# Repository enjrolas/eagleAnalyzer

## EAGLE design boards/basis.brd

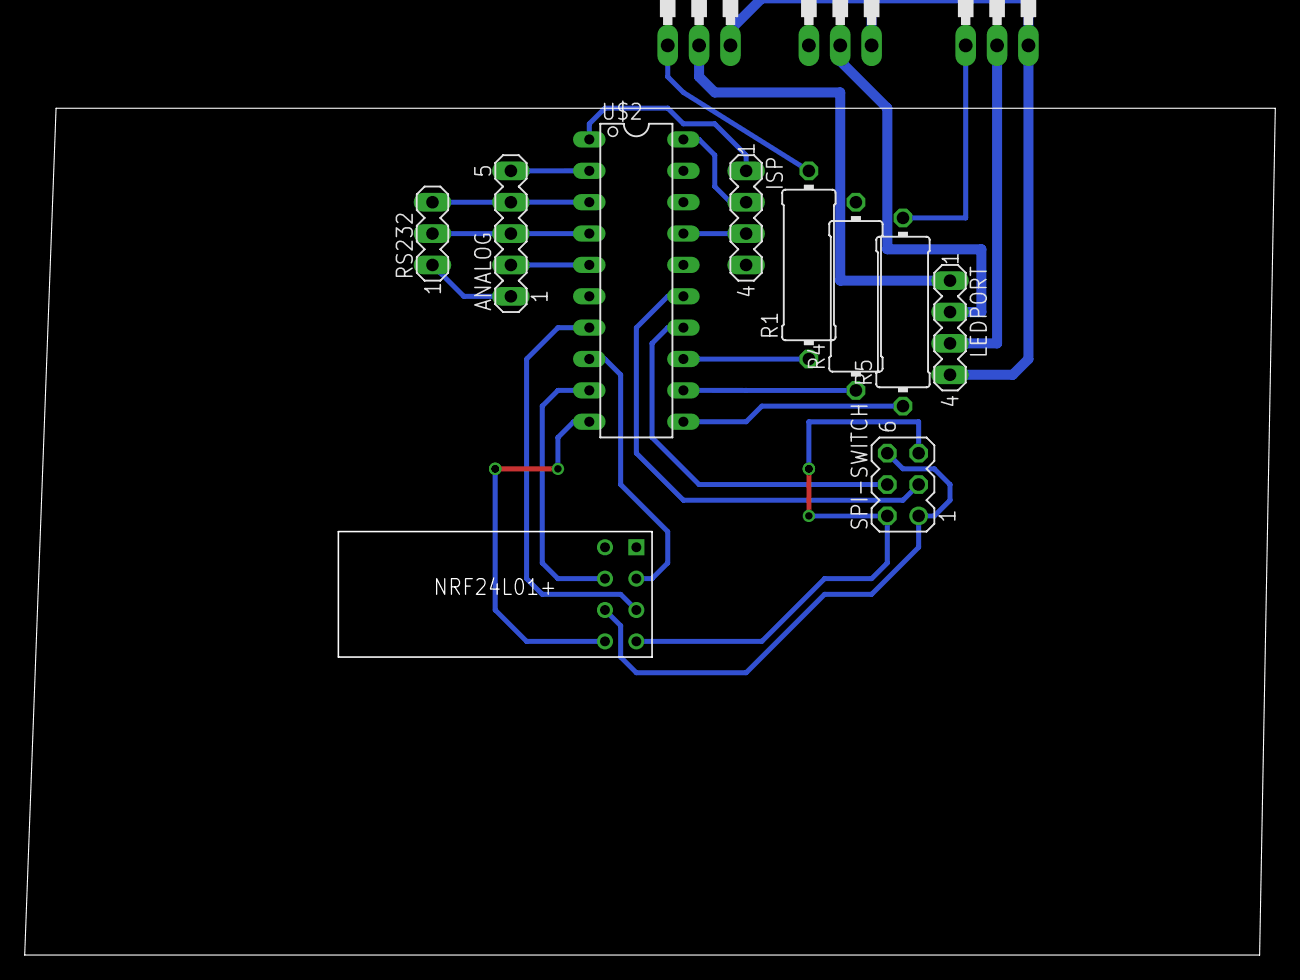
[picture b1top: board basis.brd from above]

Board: 2 copper layers, 13 parts (0 on the bottom side), 25 nets.

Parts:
ANALOG: 5PIN; MA05-1
ISP: 4PIN; MA04-1
LEDB: TIP122; TO220
LEDG: TIP122; TO220
LEDPORT: 4pin; MA04-1
LEDR: TIP122; TO220
R1, R4, R5: 1K; 0414/15
RS232: SERIAL; MA03-1
SPI-SWITCH: SPI; MA03-2
U$1: NFR24L01+-PRINT; MINI-PCB
U$2: G2XX3---N20; N20

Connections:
GND: ANALOG.1, ISP.2, LEDB.3, LEDG.3, LEDPORT.4, LEDR.3, RS232.1, U$1.GND, U$2.20
unnamed: U$1.SCK, U$2.7
unnamed: SPI-SWITCH.2, SPI-SWITCH.5, U$1.MISO
unnamed: SPI-SWITCH.4, U$2.14
unnamed: U$1.CE, U$2.8
unnamed: U$1.CSN, U$2.9
unnamed: U$1.IRQ, U$2.10
unnamed: SPI-SWITCH.3, U$2.15
unnamed: SPI-SWITCH.1, SPI-SWITCH.6, U$1.MOSI
unnamed: ANALOG.5, U$2.2
unnamed: ANALOG.4, RS232.3, U$2.3
unnamed: ANALOG.3, RS232.2, U$2.4
unnamed: ANALOG.2, U$2.5
unnamed: LEDR.1, R1.2
unnamed: LEDG.1, R4.2
unnamed: LEDB.1, R5.2
unnamed: R1.1, U$2.13
unnamed: R4.1, U$2.12
unnamed: R5.1, U$2.11
unnamed: LEDPORT.1, LEDR.2
unnamed: LEDG.2, LEDPORT.2
unnamed: LEDB.2, LEDPORT.3
TEST: ISP.3, U$2.17
VCC: ISP.1, U$1.VCC, U$2.1
_REST: ISP.4, U$2.16

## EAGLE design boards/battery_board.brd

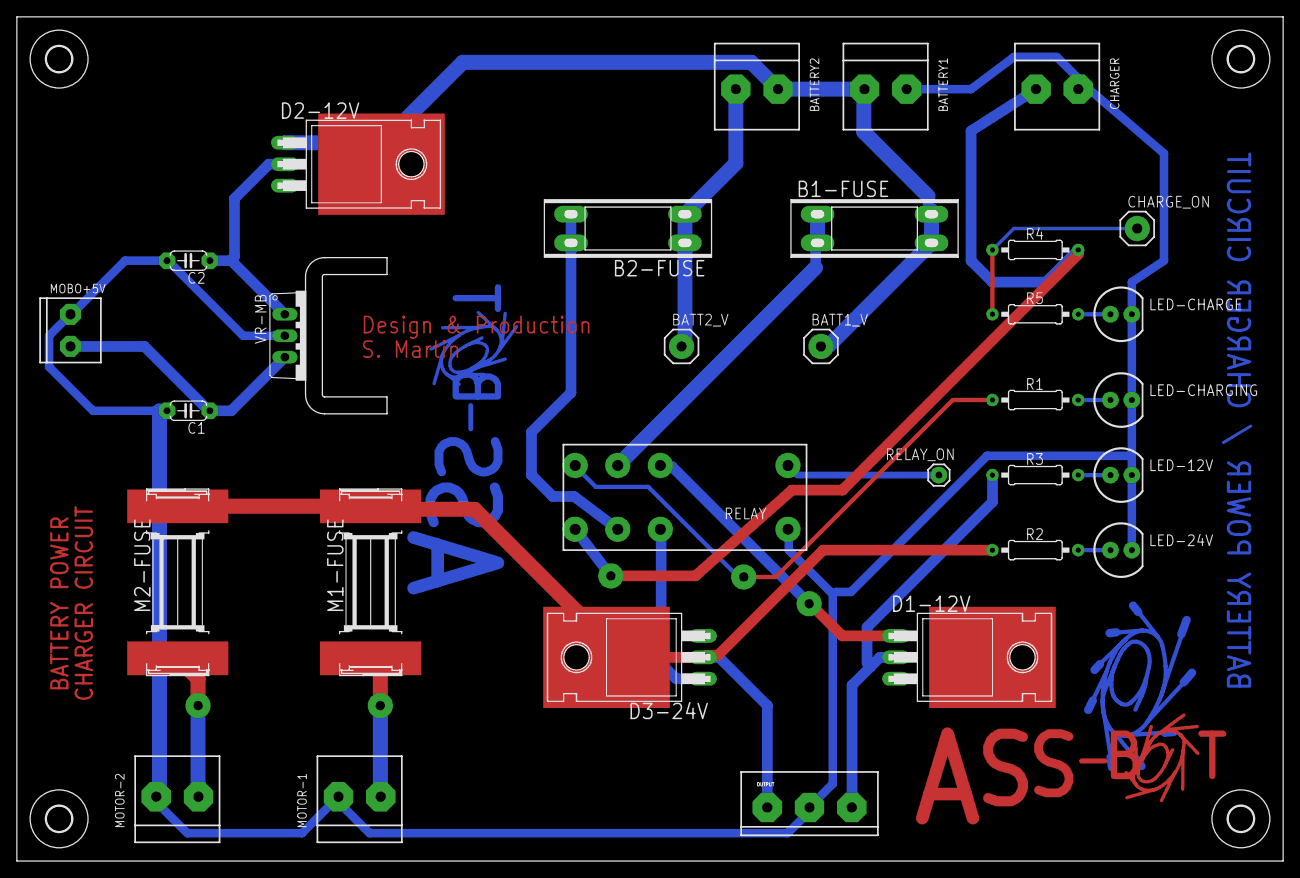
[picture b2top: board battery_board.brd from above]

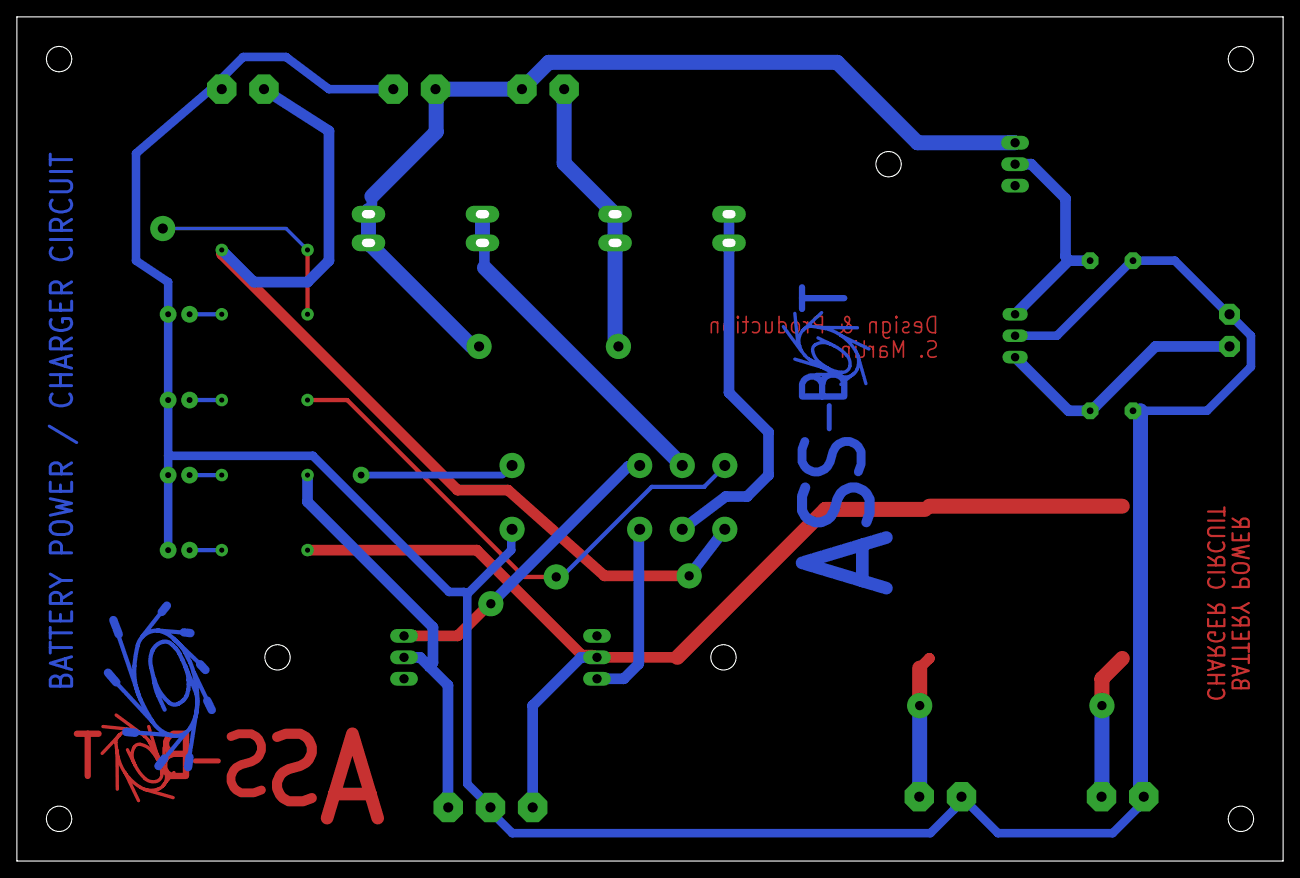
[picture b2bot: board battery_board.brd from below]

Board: 2 copper layers, 150.0 x 100.0 mm, 39 parts (2 on the bottom side), 21 nets.

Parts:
B1-FUSE, B2-FUSE: 20A; FUSE_BLADE
BATT1_V, BATT2_V: 1-HOLE; 1-HOLE_BIG
BATTERY1, BATTERY2: 12V; SCREWTERMINAL-5MM-2
C1: 10uF; C050-024X044
C2: 2.2uF; C050-024X044
CHARGER: 24V; SCREWTERMINAL-5MM-2
CHARGE_ON: 1-HOLE; 1-HOLE_BIG
D1-12V, D2-12V, D3-24V: 30A; TO22-DIODE-H
LED-12V, LED-24V: LED5MM
LED-CHARGE: LED5MM
LED-CHARGING: LED5MM
M1-FUSE, M2-FUSE: 3A; FUSE-5X20MM_SMD
MOBO+5V: 2-HOLESSC3.81MM; SCREWTERMINAL-3.81MM
MOTOR-1, MOTOR-2: 2-HOLESSC5MM; SCREWTERMINAL-5MM-2
OUTPUT: 3-HOLE; SCREWTERMINAL-5MM-3
R1, R3: 560R; 0207/10
R2, R4: 1k; 0207/10
R5: 220R; 0207/10
RELAY: 5V; RELAY_RT2
RELAY_ON: 1-HOLE"; 1-HOLE
U$1, U$7: LOGO-ASSBOT
U$3, U$4, U$5, U$6: 3,0
U$8: LOGO-SYNCHROTRON
U$9: LOGO-SYNCHROTRON-SILK
VR-MB: LT323A; TO220V-HEATSINK

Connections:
12V: D1-12V.P$2, OUTPUT.3, R3.1
24V: D3-24V.P$2, M1-FUSE.P$2, M2-FUSE.P$2, OUTPUT.1, R2.1
GND: BATTERY1.1, C1.2, C2.2, CHARGER.1, LED-12V.K, LED-24V.K, LED-CHARGE.K, LED-CHARGING.K, MOBO+5V.1, MOTOR-1.1, MOTOR-2.1, OUTPUT.2, RELAY.A2, VR-MB.2
unnamed: B1-FUSE.P$2, BATT1_V.P$1, BATTERY1.2, BATTERY2.1, D2-12V.P$1
unnamed: CHARGER.2, R4.2, RELAY.24
unnamed: LED-24V.A, R2.2
unnamed: D3-24V.P$1, RELAY.22
unnamed: B2-FUSE.P$1, BATT2_V.P$1, BATTERY2.2
unnamed: D1-12V.P$1, RELAY.12
unnamed: LED-CHARGING.A, R1.1
unnamed: C1.1, MOBO+5V.2, VR-MB.3
unnamed: M1-FUSE.P$1, MOTOR-1.2
unnamed: M2-FUSE.P$1, MOTOR-2.2
unnamed: RELAY.A1, RELAY_ON.1
unnamed: C2.1, D2-12V.P$2, VR-MB.1
unnamed: R1.2, RELAY.14
unnamed: LED-12V.A, R3.2
unnamed: CHARGE_ON.P$1, R4.1, R5.2
unnamed: LED-CHARGE.A, R5.1
unnamed: B2-FUSE.P$2, RELAY.21
unnamed: B1-FUSE.P$1, RELAY.11

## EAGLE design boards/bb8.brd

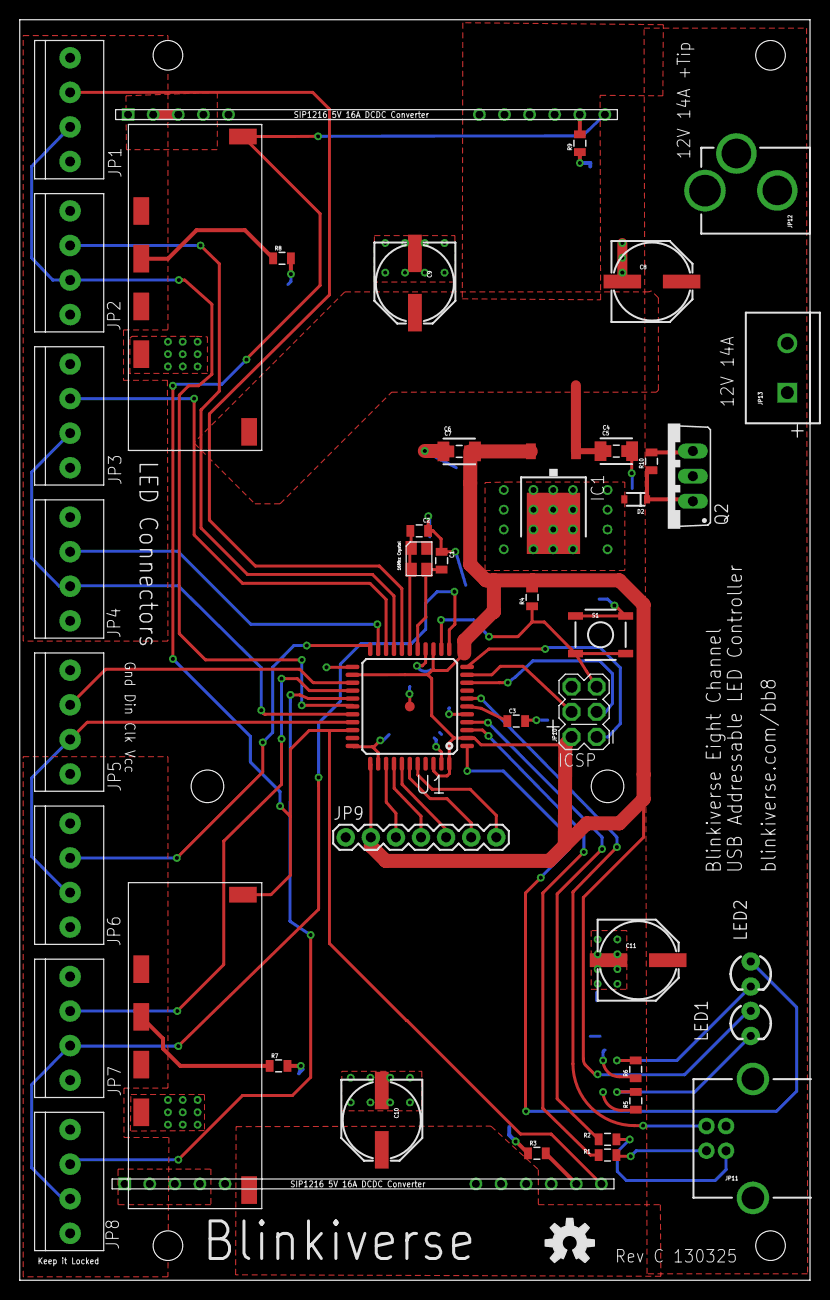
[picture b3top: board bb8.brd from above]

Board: 2 copper layers, 80.0 x 127.6 mm, 49 parts (0 on the bottom side), 44 nets.

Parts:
C1, C2: 16pF; 0805
C3: 1uF; 0805
C4: .3uF; 1210
C5: .3uF; 0805
C6: .1uF; 1210
C7: .1uF; 0805
C8, C9, C10, C11: PANASONIC_E
D2: ZENER; SOD-323
IC1: 7805; TO252
JP1, JP2, JP3, JP4, JP5, JP6, JP7, JP8: 1X4-3.5MM; 1X04-3.5MM
JP9: 1X07
JP10: 2X3_POGO
JP11: USB-B; USB-B-PTH
JP12: VIN; POWER_JACK_PTH_LOCK
JP13: SCREWTERMINAL-5MM-2
LED1: PWR; LED3MM
LED2: DATA; LED3MM
Q1: 16Mhz Crystal; XS3225
Q2: TO220BV
R1, R2: 22; 0805
R3, R7, R8, R9: 1.47k 1%; 0805
R4, R5, R6: 10k; 0805
R10: 15k; 0805
S1: RESET; TACTILE_SWITCH_SMD
U1: Atmega32U4; ARDUINO_LEONARDO-REV3B_SMARTPRJ_TQFP44-PAD
U$1, U$2: SMT1216-SIP1216_DCDCSMT; SMT1216_DCDC
U$3, U$4: SMT1216-SIP1216_DCDCSIP; SIP1216_DCDC
U$12: OSHW-LOGO-M
U$13, U$14: STAND-OFF

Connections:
CLK0-1: JP1.3, JP2.3, U1.28
CLK2-3: JP3.3, JP4.3, U1.29
CLK4-5: JP5.3, JP6.3, U1.30
CLK6-7: JP7.3, JP8.3, U1.12
CNT: U1.31, U$1.2, U$2.2, U$3.11, U$4.11
D2: LED1.K, R5.2
GND: C1.1, C2.1, C3.2, C4.2, C5.1, C6.2, C7.1, C8.-, C9.-, C10.-, C11.-, D2.2, IC1.3, JP1.1, JP2.1, JP3.1, JP4.1, JP5.1, JP6.1, JP7.1, JP8.1, JP9.1, JP10.P$6, JP11.GND, Q2.D, R3.1, R5.1, R6.1, R7.2, R8.2, R9.1, S1.1, S1.2, U1.5, U1.15, U1.23, U1.33, U1.35, U1.43, U1.P$1, U$1.6, U$2.6, U$3.5, U$3.6, U$4.5, U$4.6
LED0: JP1.2, U1.18
LED1: JP2.2, U1.19
LED2: JP3.2, U1.20
LED3: JP4.2, U1.21
LED4: JP5.2, U1.25
LED5: JP6.2, U1.22
LED6: JP7.2, U1.26
LED7: JP8.2, U1.27
LED-DATA: LED2.A, U1.1
MISO: JP10.P$1, U1.11
MOSI: JP10.P$4, U1.10
unnamed: C1.2, Q1.P$3, U1.16
unnamed: C2.2, Q1.P$1, U1.17
unnamed: R2.2, U1.4
unnamed: JP11.D+, R2.1
unnamed: R1.2, U1.3
unnamed: JP11.D-, R1.1
unnamed: C3.1, U1.6
unnamed: LED2.K, R6.2
unnamed: JP9.3, U1.36
unnamed: JP9.4, U1.37
unnamed: JP9.5, U1.38
unnamed: JP9.6, U1.39
unnamed: JP9.7, U1.40
unnamed: D2.1, Q2.G, R10.1
unnamed: R9.2, U$4.10
unnamed: R7.1, U$2.4
unnamed: R3.2, U$3.10
unnamed: R8.1, U$1.4
PSGND: JP12.GND, JP12.GNDBREAK, JP13.2, Q2.S, R10.2
RST: JP10.P$5, R4.1, S1.3, S1.4, U1.13
SCLK: JP10.P$3, U1.9
VCC: C6.1, C7.2, IC1.2, JP9.2, JP10.P$2, LED1.A, R4.2, U1.2, U1.14, U1.24, U1.34, U1.42, U1.44
VIN: C4.1, C5.2, C8.+, C9.+, C10.+, C11.+, IC1.1, JP12.PWR, JP13.1, U$1.1, U$2.1, U$3.7, U$3.8, U$4.7, U$4.8
VOUT: JP1.4, JP2.4, JP3.4, JP4.4, U$1.3, U$1.5, U$4.1, U$4.2, U$4.3, U$4.4
VOUT2: JP5.4, JP6.4, JP7.4, JP8.4, U$2.3, U$2.5, U$3.1, U$3.2, U$3.3, U$3.4
VUSB: JP11.VBUS, U1.7

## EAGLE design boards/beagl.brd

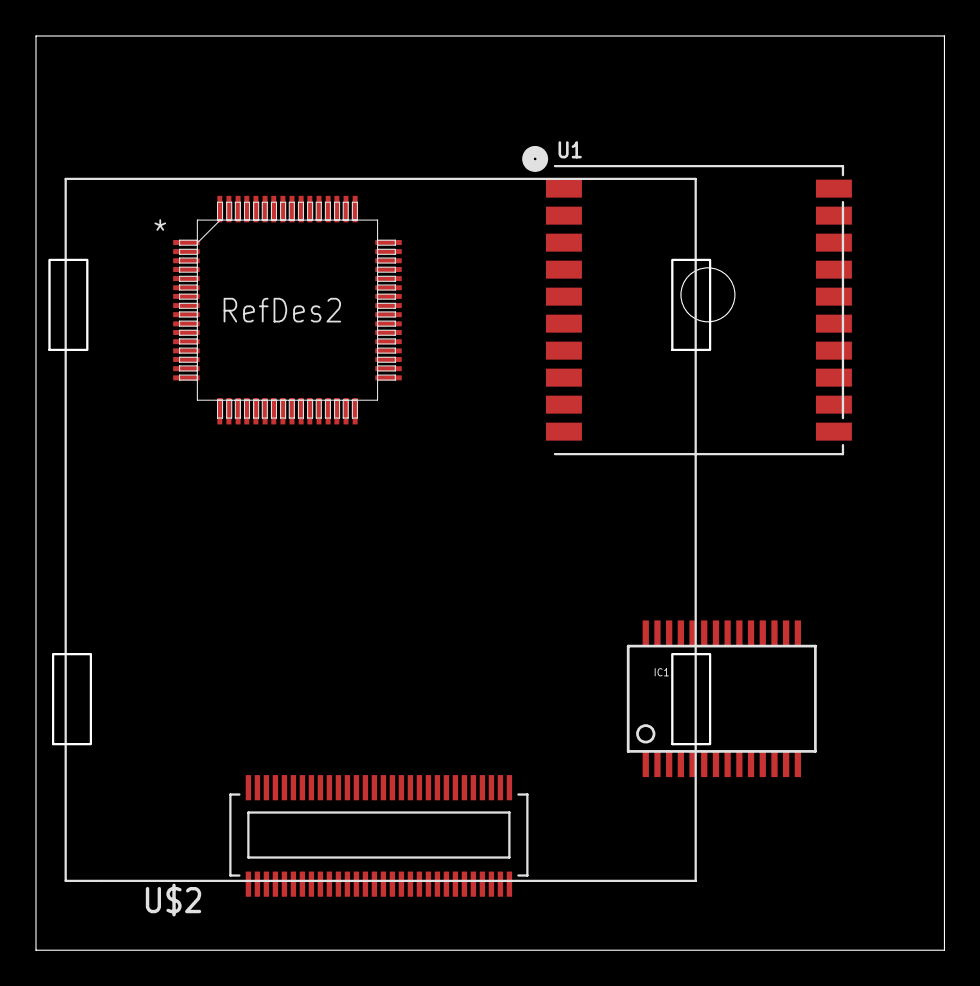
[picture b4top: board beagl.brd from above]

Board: 2 copper layers, 50.5 x 50.8 mm, 4 parts (0 on the bottom side), 4 nets, no tracks yet.

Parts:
IC1: FT232RLSSOP; SSOP28DB
U1: FGPMMOPA6H
U$1: PIC24FJ256GB206-; TQFP64_10X10MC
U$2: SM5100B

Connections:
unnamed: IC1.1, U$1.44
unnamed: IC1.5, U$1.45
unnamed: IC1.3, U$1.46
unnamed: IC1.11, U$1.43

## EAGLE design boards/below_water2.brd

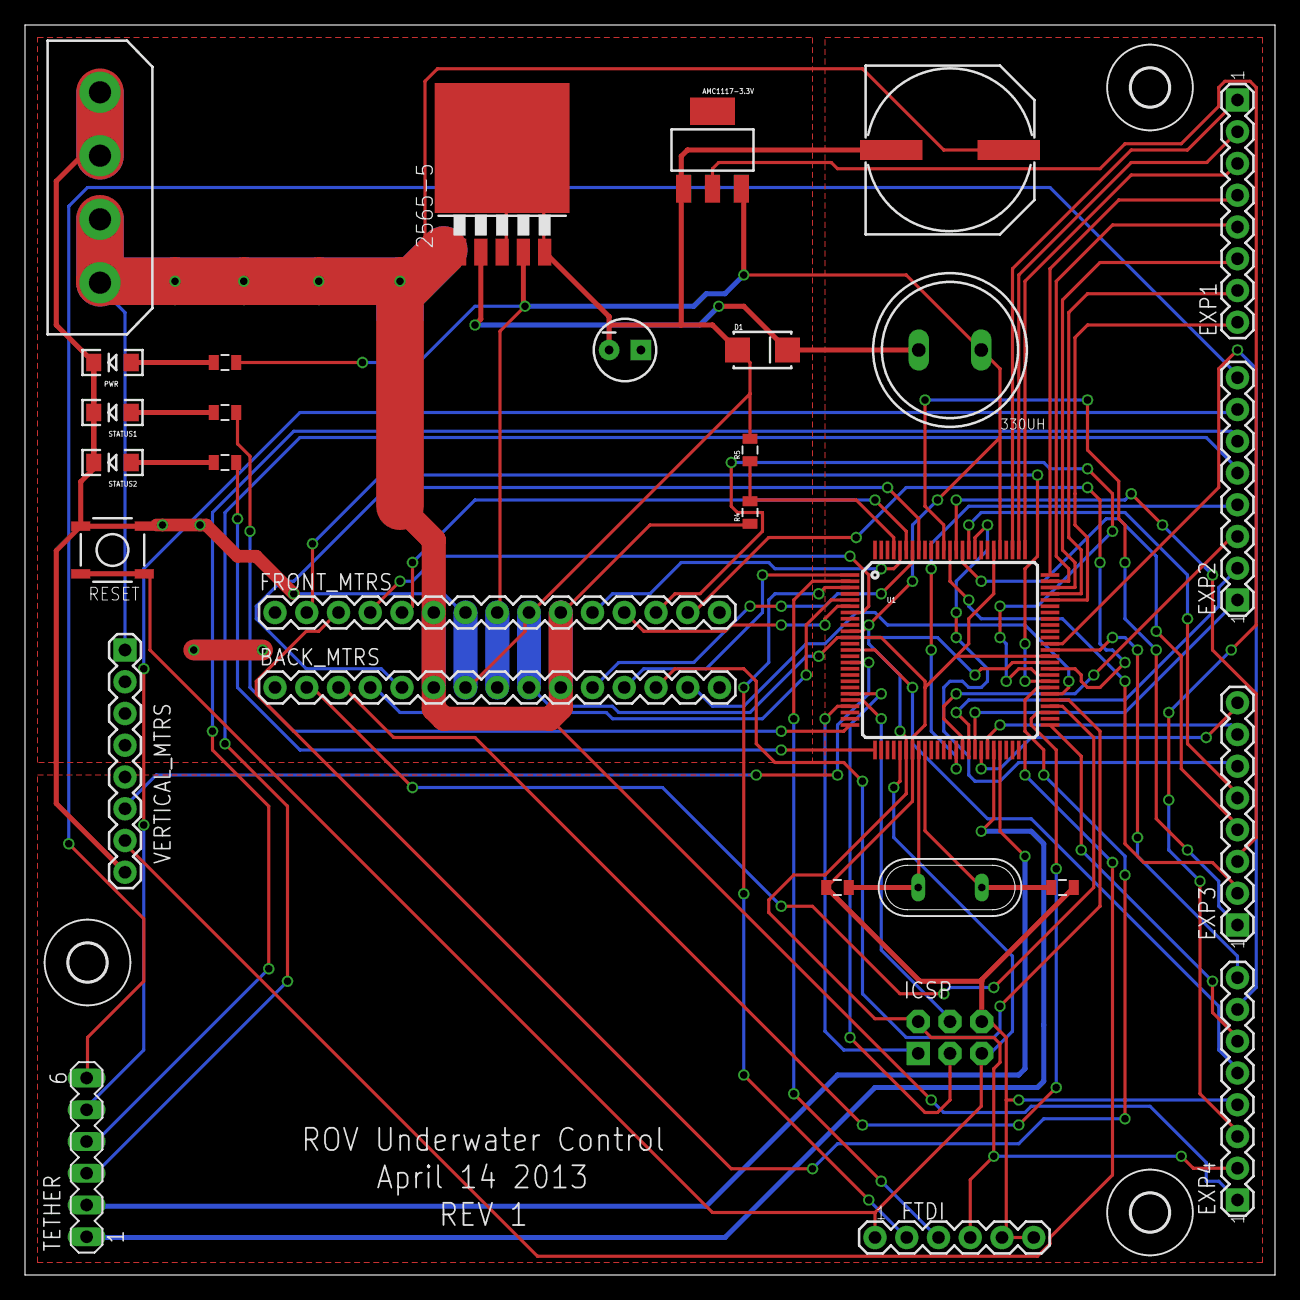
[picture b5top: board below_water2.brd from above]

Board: 2 copper layers, 100.0 x 100.0 mm, 33 parts (0 on the bottom side), 67 nets.

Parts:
330UH: SD12_1000
2565-5: TO263-5
AMC1117-3.3V: SOT223
BACK_MTRS: M15; 1X15
C1: 100uf; PANASONIC_H13
C2: 330uf; CPOL-RADIAL-10UF-25V
C3, C4: 22pf; 0805
D1: 1N5819; SMA-DIODE_ALT
EXP1, EXP2, EXP3, EXP4: 1X08
FRONT_MTRS: M15; 1X15
FTDI: 1X06
H1, H2, H3: MOUNT-HOLE3.0; 3,0
ICSP: AVR_SPI_PRG_6NS; 2X3-NS
POWER: COMPUTER-PERIPHERAL-POWER
PWR: LED-1206
Q1: 16mHz; QS
R1, R2, R3: 1k; 0805
R4: 20k; 0805
R5: 12k; 0805
S1: TACTILE_SWITCH_SMD
STATUS1, STATUS2: LED-1206
TETHER: MA06-1
U1: ATMEGA2560AU; TQFP100
VERTICAL_MTRS: 1X08

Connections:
3.3V: AMC1117-3.3V.2, EXP4.3
5V: 330UH.2, 2565-5.4, AMC1117-3.3V.3, BACK_MTRS.8, EXP4.2, FRONT_MTRS.8, FTDI.4, ICSP.2, R3.1, U1.10, U1.31, U1.61, U1.80
A0: R4.2, R5.1, U1.97
A1: FRONT_MTRS.11, U1.96
A2: FRONT_MTRS.5, U1.95
A3: BACK_MTRS.11, U1.94
A4: BACK_MTRS.5, U1.93
A8: EXP3.1, U1.89
A9: EXP3.2, U1.88
A10: EXP3.3, U1.87
A11: EXP3.4, U1.86
A12: EXP3.5, U1.85
A13: EXP3.6, U1.84
CAM1: EXP2.5, TETHER.3
CAM2: EXP2.6, TETHER.4
CAM3: EXP2.7, TETHER.5
CAM_GND: EXP2.8, TETHER.6
D2: FRONT_MTRS.12, U1.6
D3: FRONT_MTRS.4, U1.7
D4: BACK_MTRS.12, U1.1
D5: BACK_MTRS.4, U1.5
D6: U1.15, VERTICAL_MTRS.6
D12: R2.1, U1.25
D13: R1.1, U1.26
D22: EXP1.1, U1.78
D23: EXP1.2, U1.77
D24: EXP1.3, U1.76
D25: EXP1.4, U1.75
D26: EXP1.5, U1.74
D27: EXP1.6, U1.73
D28: EXP1.7, U1.72
D29: EXP1.8, U1.71
D30: FRONT_MTRS.14, U1.60
D31: FRONT_MTRS.13, U1.59
D32: FRONT_MTRS.2, U1.58
D33: FRONT_MTRS.3, U1.57
D34: BACK_MTRS.14, U1.56
D35: BACK_MTRS.13, U1.55
D36: BACK_MTRS.2, U1.54
D37: BACK_MTRS.3, U1.53
D38: U1.50, VERTICAL_MTRS.7
D42: EXP2.1, U1.42
D43: EXP2.2, U1.41
D44: EXP2.3, U1.40
D45: EXP2.4, U1.39
D50: ICSP.1, U1.22
D51: ICSP.4, U1.21
D52: ICSP.3, U1.20
GND: 2565-5.3, 2565-5.5, 2565-5.6, AMC1117-3.3V.1, BACK_MTRS.7, BACK_MTRS.9, C1.-, C2.2, C3.2, C4.2, D1.A, EXP4.4, FRONT_MTRS.7, FRONT_MTRS.9, FTDI.5, FTDI.6, ICSP.6, POWER.5V, POWER.GND, PWR.C, R5.2, S1.1, S1.2, STATUS1.C, STATUS2.C, U1.11, U1.32, U1.62, U1.81, VERTICAL_MTRS.8
unnamed: 330UH.1, 2565-5.2, D1.C
unnamed: R1.2, STATUS2.A
unnamed: R2.2, STATUS1.A
unnamed: C3.1, Q1.2, U1.33
unnamed: C4.1, Q1.1, U1.34
unnamed: PWR.A, R3.2
RESET: FTDI.1, ICSP.5, S1.3, S1.4, U1.30
RX: FTDI.3, U1.2
RX1: TETHER.1, U1.45
RX2: EXP4.6, U1.51
RX3: EXP4.8, U1.63
SCL: EXP3.8, U1.43
SDA: EXP3.7, U1.44
TX: FTDI.2, U1.3
TX1: TETHER.2, U1.46
TX2: EXP4.5, U1.13
TX3: EXP4.7, U1.64
VIN: 2565-5.1, BACK_MTRS.6, BACK_MTRS.10, C1.+, EXP4.1, FRONT_MTRS.6, FRONT_MTRS.10, POWER.12V, POWER.NC, R4.1, VERTICAL_MTRS.1

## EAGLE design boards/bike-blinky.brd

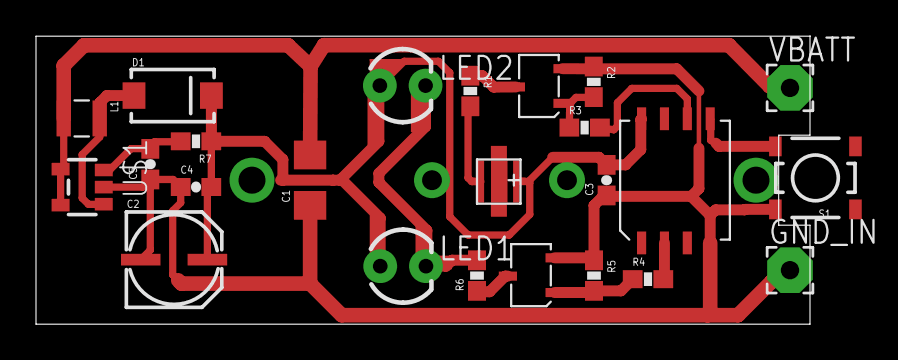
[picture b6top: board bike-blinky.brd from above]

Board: 2 copper layers, 43.0 x 16.0 mm, 24 parts (0 on the bottom side), 14 nets.

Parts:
C1: 100uF (tantalum); 1206
C2: 100uF; PANASONIC_C
C3, C4, C5: 1uF; 0603-CAP
D1: STPS2L40AF; SMA-DIODE
GND_IN: 2,54/1,0
L1: 10uH; 1007
LED1, LED2: LED3MM
LED3: XP-D; XB-D-REV1
R1: 3.9; 0603-RES
R2, R5: 100K; 0603-RES
R3, R4: 100; 0603-RES
R6: 33; 0603-RES
R7: 10; 0603-RES
S1: TACTILE_SWITCH_SMD-2
U$1: SP6641B; SOT23-5
U$2: ATTINY13; WSOIC-8
U$7, U$8: NDS351AN; SOT-23-3
VBATT: 2,54/1,0

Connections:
5V: C2.+, C3.2, C4.2, D1.C, LED1.A, LED2.A, LED3.A, R7.1, U$2.8
GND: C1.1, C2.-, C3.1, C4.1, C5.1, GND_IN.1, R2.1, R5.1, S1.1, U$1.2, U$2.4, U$7.2, U$8.2
GND_OUT: R1.1, U$8.3
GND_OUT1: R6.1, U$7.3
unnamed: R3.2, U$2.6
unnamed: D1.A, L1.1, U$1.1
unnamed: LED1.K, LED2.K, R6.2
unnamed: LED3.C, R1.2
unnamed: R4.2, U$2.2
unnamed: C5.2, R7.2, U$1.3
RED: R2.2, R3.1, U$8.1
SW: S1.2, U$2.5
VBATT: C1.2, L1.2, U$1.4, U$1.5, VBATT.1
YEL: R4.1, R5.2, U$7.1

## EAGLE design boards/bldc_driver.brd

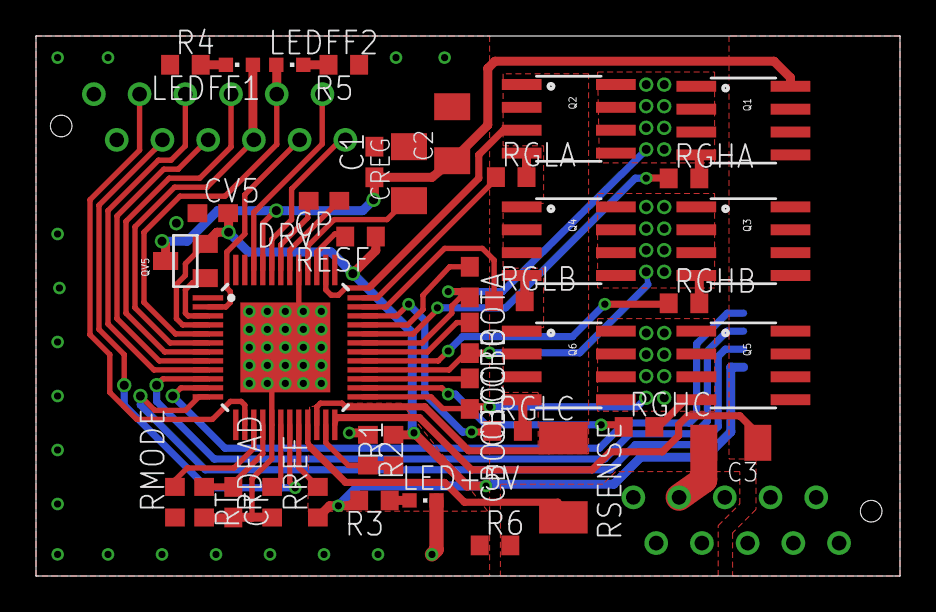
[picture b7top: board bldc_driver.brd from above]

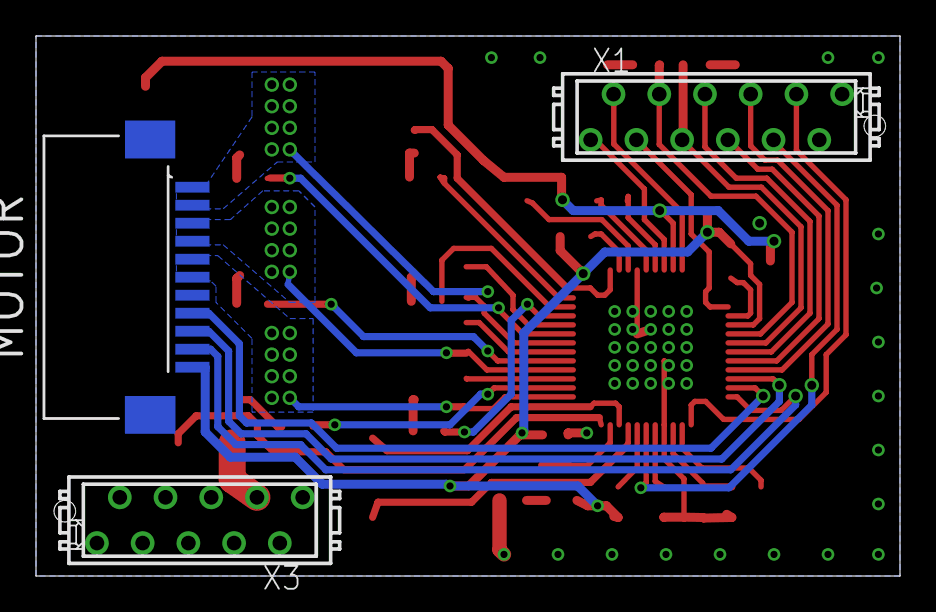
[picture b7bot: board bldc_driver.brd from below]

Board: 2 copper layers, 48.0 x 30.0 mm, 42 parts (3 on the bottom side), 49 nets.

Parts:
C1: 100nF; C0603
C2, C3: 10uF; C1206K
CBOOTA: 220nF; C0603
CBOOTB: 220nF; C0603
CBOOTC: 220nF; C0603
CP: 470nF; C0603
CREG: 10uF X7R; C1206K
CT: 680pF; C0603
CV5: 220nF; C0603
DRV: A3930; LQFP-48
LED+5V: CHIPLED_0603
LEDFF1, LEDFF2: CHIPLED_0603
MOTOR: 52207-1185; MOLEX_52207-1185
Q1, Q2, Q3, Q4, Q5, Q6: MOSFET-N; SO08
QV5: SOT23
R1, R2, R3, R4, R5: 10k; R0603
R6: 1; R0603
RDEAD: 10k; R0603
RESF: 10k; R0603
RGHA: 47; R0603
RGHB: 47; R0603
RGHC: 47; R0603
RGLA: 47; R0603
RGLB: 47; R0603
RGLC: 47; R0603
RMODE: 10k; R0603
RREF: 10k; R0603
RSENSE: 0.09; R2010
RT: 56k; R0603
X1: LOGIC; MICROMATCH-12
X3: MICROMATCH-10

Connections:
+5V: CV5.2, DRV.4, MOTOR.11, QV5.2, R1.2, R3.2, RESF.1, RREF.1
+12V: C1.1, C2.1, C3.1, DRV.24, DRV.45, Q1.5, Q1.6, Q1.7, Q1.8, Q3.5, Q3.6, Q3.7, Q3.8, Q5.5, Q5.6, Q5.7, Q5.8, QV5.3, X3.1, X3.2, X3.3, X3.4, X3.5
BRAKE: DRV.8, X1.6
COAST: DRV.46, X1.11
CSOUT: DRV.19, X1.4
DIR: DRV.9, X1.5
DIRO: DRV.44, X1.12
ESF: DRV.39, RESF.2
FF1: DRV.6, LEDFF1.A, X1.8
FF2: DRV.5, LEDFF2.A, X1.9
GHA: DRV.32, RGHA.1
GHB: DRV.29, RGHB.1
GHC: DRV.26, RGHC.1
GLA: DRV.36, RGLA.1
GLB: DRV.35, RGLB.1
GLC: DRV.34, RGLC.1
GND: C1.2, C2.2, CREG.2, CT.2, CV5.1, DRV.0, DRV.17, DRV.41, LED+5V.C, MOTOR.7, MOTOR.12, MOTOR.13, R2.1, R4.1, R5.1, R6.1, RDEAD.1, RMODE.1, RT.2, X1.1, X1.2
GNDA: C3.2, DRV.21, R6.2, RSENSE.2, X3.6, X3.7, X3.8, X3.9, X3.10
H1: DRV.10, MOTOR.9
H2: DRV.11, MOTOR.8
H3: DRV.12, MOTOR.10
LSS: DRV.22, DRV.38, Q2.1, Q2.2, Q2.3, Q4.1, Q4.2, Q4.3, Q6.1, Q6.2, Q6.3, RSENSE.1
unnamed: Q1.4, RGHA.2
unnamed: Q2.4, RGLA.2
unnamed: Q3.4, RGHB.2
unnamed: Q4.4, RGLB.2
unnamed: Q5.4, RGHC.2
unnamed: Q6.4, RGLC.2
unnamed: CBOOTA.1, DRV.33
unnamed: CREG.1, DRV.40
unnamed: CT.1, DRV.16, RT.1
unnamed: CP.1, DRV.42
unnamed: CP.2, DRV.43
unnamed: CBOOTB.1, DRV.30
unnamed: DRV.18, RDEAD.2
unnamed: CBOOTC.1, DRV.27
unnamed: LED+5V.A, R3.1
unnamed: DRV.20, RREF.2
unnamed: DRV.15, RMODE.2
unnamed: LEDFF1.C, R4.2
unnamed: LEDFF2.C, R5.2
unnamed: DRV.3, QV5.1
PWM: DRV.14, X1.3
RESET: DRV.2, X1.10
SA: CBOOTA.2, DRV.31, MOTOR.1, MOTOR.2, Q1.1, Q1.2, Q1.3, Q2.5, Q2.6, Q2.7, Q2.8
SB: CBOOTB.2, DRV.28, MOTOR.3, MOTOR.4, Q3.1, Q3.2, Q3.3, Q4.5, Q4.6, Q4.7, Q4.8
SC: CBOOTC.2, DRV.25, MOTOR.5, MOTOR.6, Q5.1, Q5.2, Q5.3, Q6.5, Q6.6, Q6.7, Q6.8
TACHO: DRV.7, X1.7
VDSTH: DRV.23, R1.1, R2.2

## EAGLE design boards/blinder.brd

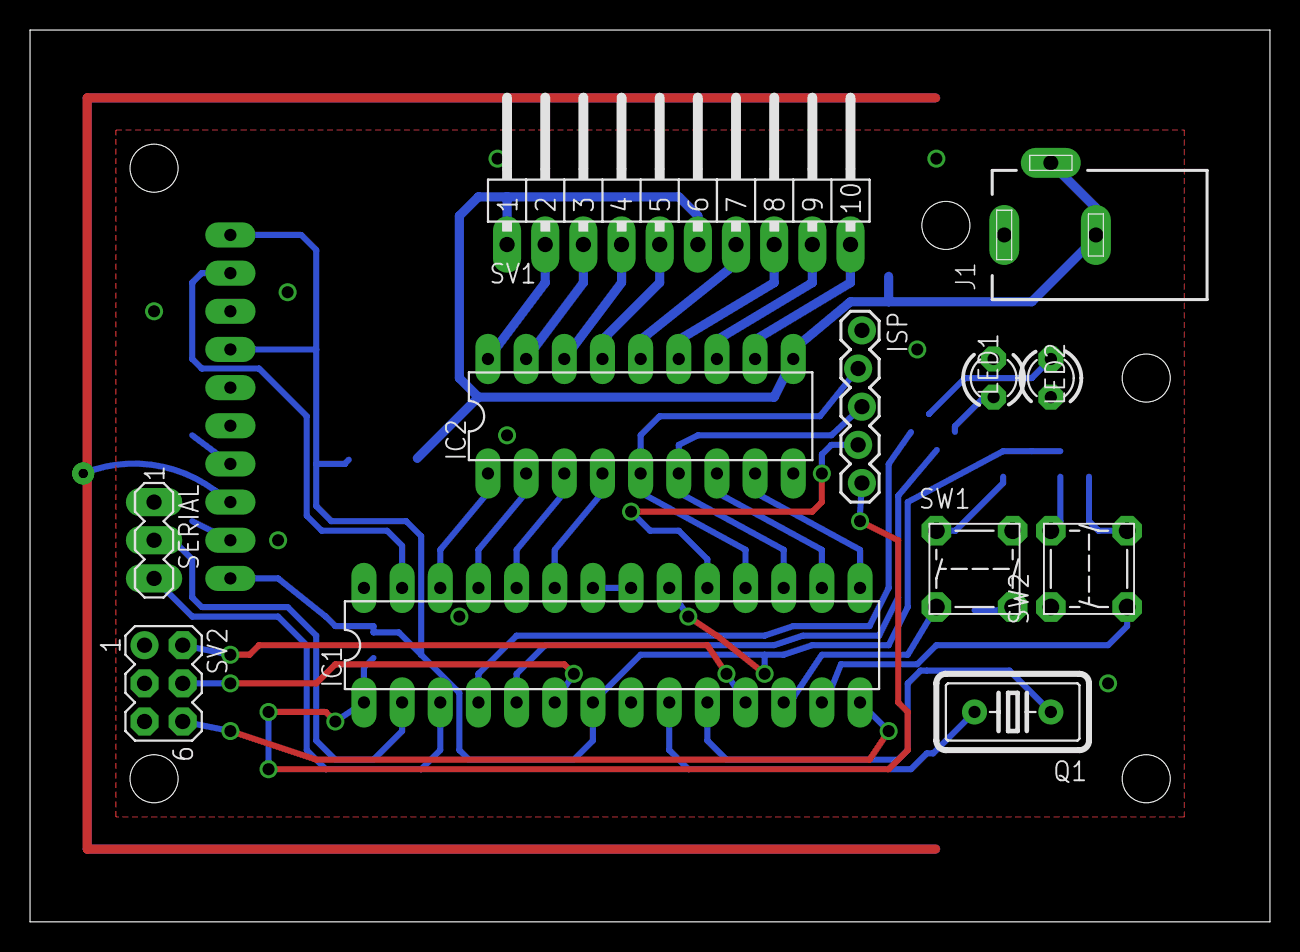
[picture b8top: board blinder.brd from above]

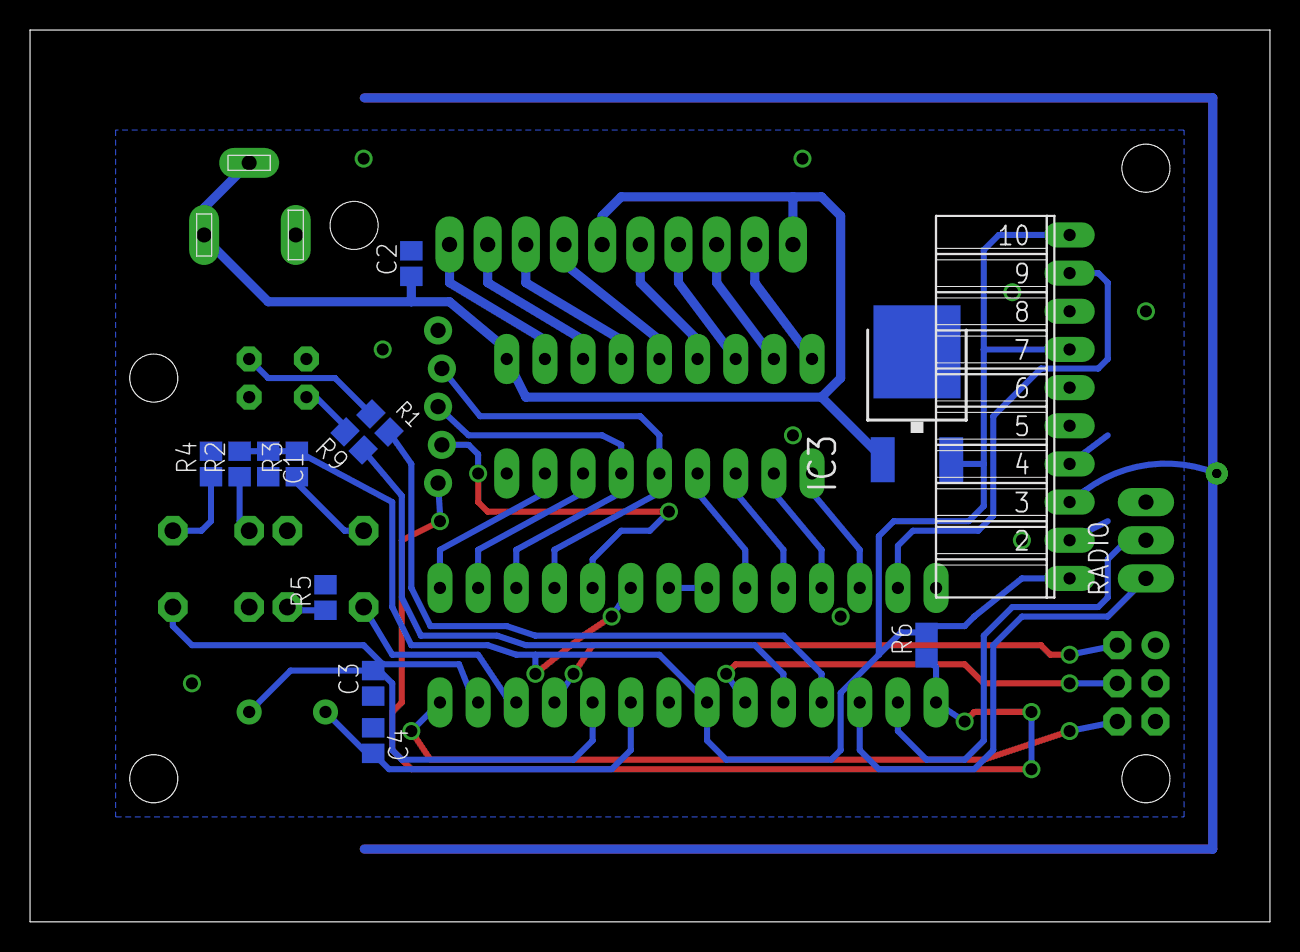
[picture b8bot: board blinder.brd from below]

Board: 2 copper layers, 82.5 x 59.4 mm, 27 parts (14 on the bottom side), 40 nets.

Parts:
C1: 100n; C0805
C2: 470n; C0805
C3, C4: 22p; C0805
IC1: ATMEGA328PU; DIL28-3
IC2: ULN2803AFWG; DIL18
IC3: 78M05SMD; DPACK
ISP: 1X05_LOCK
J1: DCJ0202
LED1, LED2: LED3MM
Q1: 16M; HC18U-V
R1, R9: 1k; R0805
R2, R3: 2k; R0805
R4, R5, R6: 10k; R0805
RADIO: FE10W
SERIAL: MA03-1
SV1: Motors; MA10-1W
SV2: MA03-2
SW1, SW2: TS
U$1, U$2: ANT44350H; DIPOLEHALF443.95_50

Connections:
+12V: C2.1, IC2.10, IC3.1, J1.2, J1.3, SV1.1, SV1.6
ANTENNA: RADIO.3, U$1.FEED, U$2.FEED
DEBUG0: IC1.14, SV2.6
DEBUG1: IC1.6, SV2.4
DEBUG2: IC1.11, SV2.2
GND: C1.2, C2.2, C3.1, C4.1, IC1.8, IC1.21, IC1.22, IC2.9, IC3.4, ISP.1, J1.1, LED1.K, LED2.K, R4.2, R5.2, RADIO.2, RADIO.4, RADIO.6, SERIAL.1, SV2.1, SV2.3, SV2.5
LED1: IC1.4, R1.1
LED2: IC1.5, R9.1
MISO/MOT3: IC1.18, IC2.5, ISP.2
MOSI/MOT2: IC1.17, IC2.6, ISP.3
MOT0: IC1.15, IC2.8
MOT0_12: IC2.11, SV1.10
MOT1: IC1.16, IC2.7
MOT1_12: IC2.12, SV1.9
MOT2_12: IC2.13, SV1.8
MOT3_12: IC2.14, SV1.7
MOT4: IC1.23, IC2.4
MOT4_12: IC2.15, SV1.5
MOT5: IC1.24, IC2.3
MOT5_12: IC2.16, SV1.4
MOT6: IC1.25, IC2.2
MOT6_12: IC2.17, SV1.3
MOT7: IC1.26, IC2.1
MOT7_12: IC2.18, SV1.2
unnamed: LED1.A, R1.2
unnamed: LED2.A, R9.2
unnamed: R5.1, SW1.3
unnamed: R4.1, SW2.3
unnamed: R3.1, SW1.1
unnamed: R2.1, SW2.2
RADIO_RX: IC1.27, RADIO.9
RESET: IC1.1, ISP.5, R6.1
RX: IC1.2, SERIAL.2
SCK: IC1.19, ISP.4
SW1: IC1.12, SW1.4
SW2: IC1.13, SW2.4
TX: IC1.3, SERIAL.3
VCC: C1.1, IC1.7, IC1.20, IC3.3, R2.2, R3.2, R6.2, RADIO.1, RADIO.7, RADIO.10
XTAL1: C4.2, IC1.9, Q1.2
XTAL2: C3.2, IC1.10, Q1.1

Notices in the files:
parts and their libraries:
SparkFun-Connectors: Licensing: CC v3.0 Share-Alike You are welcome to use this library for commercial purposes.
